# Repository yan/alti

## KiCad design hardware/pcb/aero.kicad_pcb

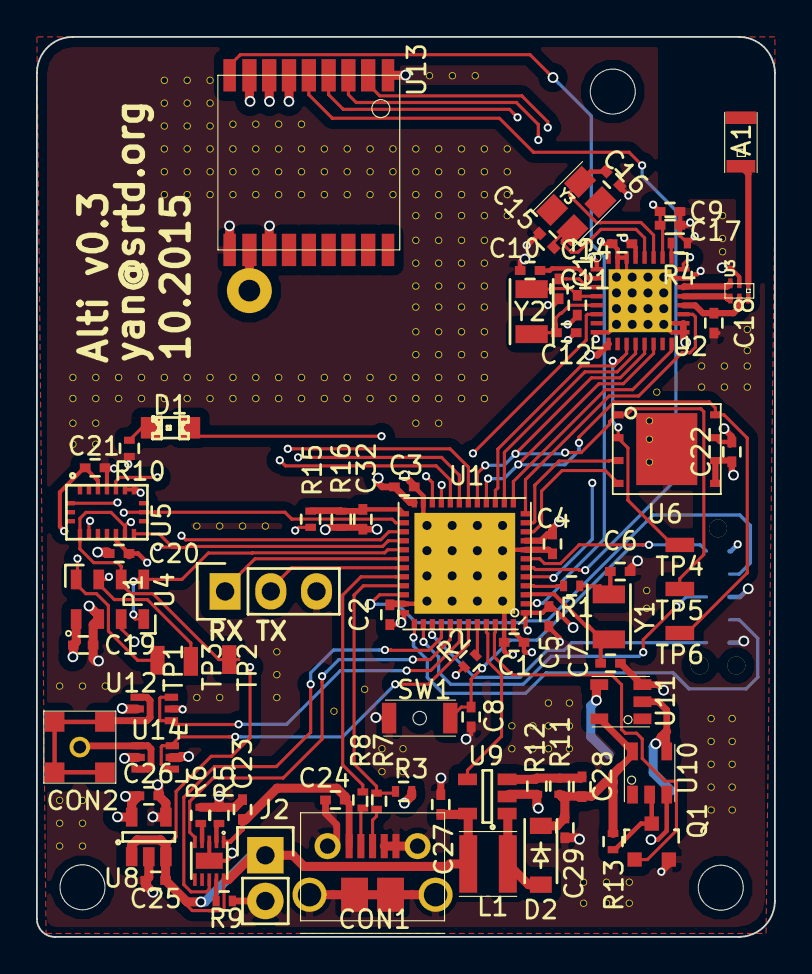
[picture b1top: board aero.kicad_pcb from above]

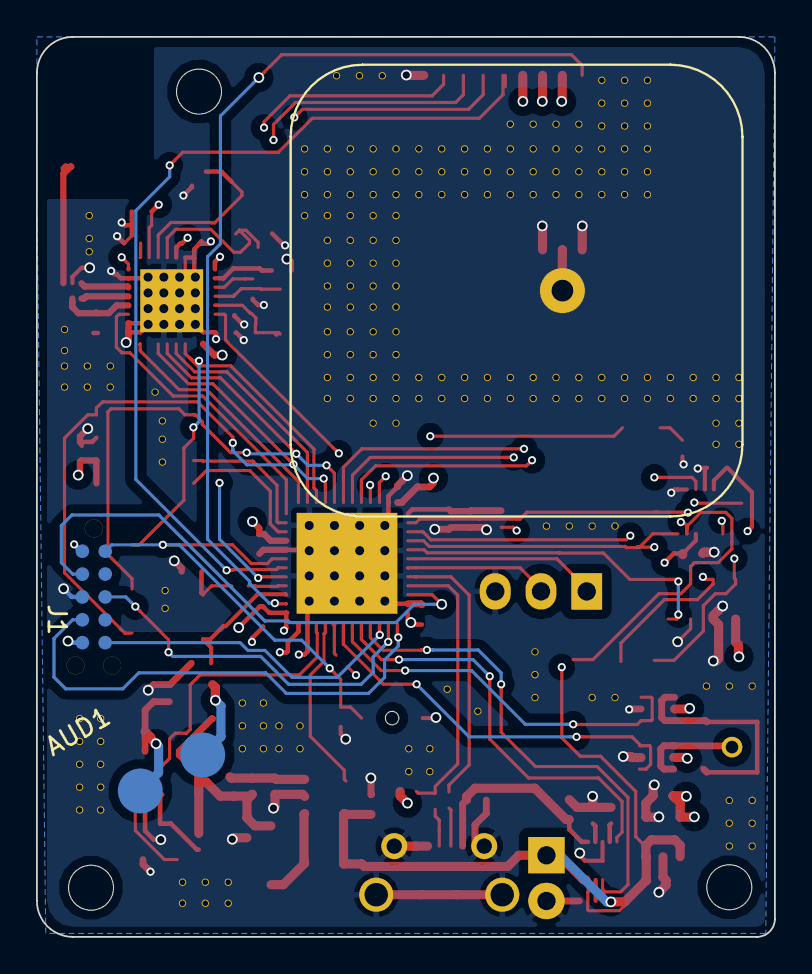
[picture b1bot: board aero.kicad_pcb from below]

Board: 4 copper layers, 41.0 x 50.0 mm, 81 parts (3 on the bottom side), 70 nets.

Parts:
A1: 2450AT18A100
A2: U.FL_Antenna; CGGP.25.4.A.02
AUD1: PIEZO; Piezo_Solder_Conn
C1, C2, C3, C4, C9, C10, C14, C19, C20, C21, C22, C29, C32: 100nF; C_0402
C5, C23, C24, C25: 1uF; C_0402
C6, C7: 9pF; C_0402
C8: 10nF; C_0402
C11, C12: 15pF; C_0402
C13: 33nF; C_0402
C15, C16: 12pF; C_0402
C17: 1.0nF; C_0402
C18: 2.2nF; C_0402
C26: 2.2uF; C_0402
C27: 4.7uF; C_0402
C28: 22pF; C_0402
CON1: USB-MICRO-B; WM1399CT-ND
CON2: MMCX_CONN; CONMMCX002-SMD
D1: LED; LED-0805
D2: D_Schottky; SOD-123
J1: CORTEX_DBG_CONN; TC2050-IDC-NL
J2: LiPoly_Conn; Pin_Header_Straight_1x02
L1: 10u; IND-744029100
P1: CONN_01X03; Pin_Header_Straight_1x03
Q1: BSS138; SOT-23
R1: 0; R_0402
R2, R9: 10k; R_0402
R3: 1.5k; R_0402
R4: 22k; R_0402
R5: 825; R_0402
R6: 2k; R_0402
R7, R8: 22; R_0402
R10: 200; R_0402
R11: 2.21m; R_0402
R12: 309k; R_0402
R13: 30k; R_0402
R15, R16: 10m; R_0402
SW1: SW_PUSH; B3U-1000P
TP1, TP2, TP3, TP4, TP5, TP6: Test_Point; TP_0603
U1: STM32L151C8; UFQFPN48
U2: nRF8001; QFN-32-1EP_5x5mm_Pitch0.5mm
U3: 2450BM14A0002
U4: ms5611
U5: BMX055
U6: AT45DB321E; UDFN-8
U7: BQ24040DSQ; WSON-10-1EP
U8: TPS783; SOT-23-5
U9: TPS61041; SOT-23-5
U10, U11: BU4SU69G2; SSOP-5
U12, U14: NC7WZ17; SC-70-6
U13: u-blox_max-7c/q; ublox_MAX7
Y1: Crystal; Crystal_32768_FC-135R
Y2: 32.768KHz; Crystal_32768_FC-135R
Y3: 16MHz; Crystal_TSX_3225

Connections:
+3V: C1.1, C2.1, C3.1, C4.1, C5.1, C9.1, C14.1, C17.1, C19.1, C20.1, C21.1, C22.1, C26.1, J1.1, R3.1, U1.1, U1.9, U1.24, U1.36, U1.48, U2.1, U2.9, U2.24, U2.26, U2.29, U4.1, U5.3, U5.13, U6.5, U6.6, U8.5, U12.5, U13.6, U13.7, U13.8, U14.5
+10V: C28.1, C29.1, D2.1, R11.1, R13.1, U10.5, U11.5
/GPS/EXT_INT: U1.6, U13.5
/GPS/RESET: U1.2, U13.9
/GPS/TIMEPULSE: U1.5, U13.4
/at45db321e/MISO: TP6.1, U1.16, U2.14, U6.8
/at45db321e/MOSI: TP5.1, U1.17, U2.13, U6.1
/at45db321e/SCK: TP4.1, U1.15, U2.11, U6.2
/at45db321e/~CS: U1.10, U6.4
/at45db321e/~RESET: U1.11, U6.3
/bmx055/ACC_SEL: U1.18, U5.16
/bmx055/GYRO_SEL: U1.19, U5.5
/bmx055/MAG_SEL: U1.20, U5.20
/bmx055/MISO: TP2.1, U1.27, U4.6, U5.12, U5.17
/bmx055/MOSI: TP3.1, U1.28, U4.7, U5.11
/bmx055/SCK: TP1.1, U1.26, U4.8, U5.9
/nRF8001/~RDYN: U1.13, U2.16
/nRF8001/~REQN: U1.14, U2.12
/nRF8001/~RESET: U1.12, U2.19
/power/USB_D+: R3.2, R8.1, U1.33
/power/USB_D-: R7.1, U1.32
/warn/PIEZO_EN: U1.45, U9.4
/warn/PIEZO_OUT: Q1.1, U1.46
/warn/STATUS_LED: D1.2, U1.22
/warn/WARN_LED_A: U1.42, U12.1, U12.3
/warn/WARN_LED_B: U1.43, U14.1, U14.3
BATT_SENSE: C32.2, R15.1, R16.2, U1.25
GND: C1.2, C2.2, C3.2, C4.2, C5.2, C6.2, C7.1, C8.2, C9.2, C10.2, C11.2, C12.2, C13.2, C14.2, C15.1, C16.1, C17.2, C18.2, C19.2, C20.2, C21.2, C22.2, C23.2, C24.2, C25.2, C26.2, C27.2, C29.2, C32.1, CON1.4, CON1.5, CON1.6, CON1.7, CON1.8, CON1.9, CON1.10, CON1.11, J1.3, J1.5, J2.2, P1.3, Q1.2, R2.2, R4.1, R5.2, R6.2, R9.1, R10.1, R12.2, R16.1, SW1.2, U1.8, U1.23, U1.35, U1.47, U1.49, U2.8, U2.17, U2.18, U2.23, U2.30, U2.31, U2.33, U3.2, U4.2, U4.3, U5.4, U5.6, U5.7, U6.7, U7.3, U7.11, U8.2, U8.4, U9.2, U10.3, U11.3, U12.2, U13.1, U13.10, U13.12, U14.2
GPS_RX: P1.1, U1.30, U13.3
GPS_TX: P1.2, U1.31, U13.2
MS5611_EN: U1.29, U4.4, U4.5
NRF8001_ACTIVE: U1.21, U2.6
unnamed: A1.1, U3.1
unnamed: A2.1, U13.11
unnamed: AUD1.1, U11.4
unnamed: AUD1.2, U10.4, U11.2
unnamed: C6.1, R1.1, Y1.1
unnamed: C7.2, U1.3, Y1.2
unnamed: C10.1, U2.2
unnamed: C11.1, U2.4, Y2.1
unnamed: C12.1, U2.5, Y2.2
unnamed: C13.1, U2.3
unnamed: C15.2, U2.28, Y3.1
unnamed: C16.2, U2.27, Y3.2
unnamed: C18.1, U2.20, U3.5
unnamed: C23.1, C24.1, CON1.1, U7.1
unnamed: C28.2, R11.2, R12.1, U9.3
unnamed: CON1.2, R7.2
unnamed: CON1.3, R8.2
unnamed: CON2.1, U14.4, U14.6
unnamed: CON2.2, CON2.3, CON2.4, CON2.5, U12.4, U12.6
unnamed: D1.1, R10.2
unnamed: D2.2, L1.1, U9.1
unnamed: J1.2, U1.34
unnamed: J1.4, U1.37
unnamed: J1.8, U1.38
unnamed: Q1.3, R13.2, U10.2
unnamed: R1.2, U1.4
unnamed: R2.1, U1.44
unnamed: R4.2, U2.25
unnamed: R5.1, U7.2
unnamed: R6.1, U7.4
unnamed: R9.2, U7.9
unnamed: U2.21, U3.4
unnamed: U2.22, U3.3
SWO: J1.6, U1.39
Vbatt: C25.1, C27.1, J2.1, L1.2, R15.2, U7.10, U8.1, U8.3, U9.5
~CHG: U1.40, U7.8
~NRST: C8.1, J1.10, SW1.1, U1.7
~PG: U1.41, U7.5

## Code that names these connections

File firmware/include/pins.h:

#ifndef __PINS_DEF
#define __PINS_DEF
/****************************************************************/
/** AUTOGENERATED from ../include/pins.def. DO NOT EDIT *********/
/****************************************************************/

#if defined(STM32L1) && defined(OPENCM3)
#  include <stm32l1_opencm3_pins.h>
#elif defined(STM32L1) && defined(STM32_STDPERIPH_LIB)
#  include <stm32l1_stdperiphlib_pins.h>
#elif TESTING == 1
#  include <empty_pins.h>
#else
#  error "Unsupprted architecture"
#endif

#define PIEZO_OUT_TIMER                 TIM4
#define PIEZO_OUT_CHANNEL               TIM_OC(4)
#define PIEZO_OUT_AF                    GPIO_AF2
#define STATUS_LED_TIMER                TIM2
#define STATUS_LED_CHANNEL              TIM_OC(4)
#define STATUS_LED_AF                   GPIO_AF1
#define BT_STORE                        SPI1
#define BT_STORE_GPIO                   GPIO(A)
#define BT_STORE_PINS                   (PIN(7)|PIN(6)|PIN(5))
#define SENSORS                         SPI2
#define SENSORS_GPIO                    GPIO(B)
#define SENSORS_PINS                    (PIN(15)|PIN(14)|PIN(13))
#define UBLOX_UART                      USART1
#define UBLOX_UART_GPIO                 GPIO(A)
#define UBLOX_UART_PINS                 (PIN(10)|PIN(9))
#define NRF8001_LSB                     1
#define NRF8001_BUS                     BT_STORE
#define ADESTO_FLASH_LSB                1
#define ADESTO_FLASH_BUS                BT_STORE
#define MS5611_LSB                      1
#define MS5611_BUS                      SENSORS
#define BMX055_LSB                      1
#define BMX055_BUS                      SENSORS
#define UBLOX_MAX7_LSB                  1
#define UBLOX_MAX7_BUS                  UBLOX_UART
#define ADESTO_FLASH_CS                 PIN(0)
#define ADESTO_FLASH_CS_GPIO            GPIO(A)
#define ADESTO_FLASH_RESET              PIN(1)
#define ADESTO_FLASH_RESET_GPIO         GPIO(A)
#define NRF8001_RST                     PIN(2)
#define NRF8001_RST_GPIO                GPIO(A)
#define NRF8001_RDYN                    PIN(3)
#define NRF8001_RDYN_GPIO               GPIO(A)
#define NRF8001_REQN                    PIN(4)
#define NRF8001_REQN_GPIO               GPIO(A)
#define BT_STORE_SCK                    PIN(5)
#define BT_STORE_SCK_GPIO               GPIO(A)
#define BT_STORE_MISO                   PIN(6)
#define BT_STORE_MISO_GPIO              GPIO(A)
#define BT_STORE_MOSI                   PIN(7)
#define BT_STORE_MOSI_GPIO              GPIO(A)
#define MS5611_EN                       PIN(8)
#define MS5611_EN_GPIO                  GPIO(A)
#define UBLOX_UART_TX                   PIN(9)
#define UBLOX_UART_TX_GPIO              GPIO(A)
#define UBLOX_UART_RX                   PIN(10)
#define UBLOX_UART_RX_GPIO              GPIO(A)
#define BMX055_EN_ACC                   PIN(0)
#define BMX055_EN_ACC_GPIO              GPIO(B)
#define BMX055_EN_GYRO                  PIN(1)
#define BMX055_EN_GYRO_GPIO             GPIO(B)
#define BMX055_EN_MAG                   PIN(2)
#define BMX055_EN_MAG_GPIO              GPIO(B)
#define CHG                             PIN(4)
#define CHG_GPIO                        GPIO(B)
#define PG                              PIN(5)
#define PG_GPIO                         GPIO(B)
#define WARN_LED_A                      PIN(6)
#define WARN_LED_A_GPIO                 GPIO(B)
#define WARN_LED_B                      PIN(7)
#define WARN_LED_B_GPIO                 GPIO(B)
#define PIEZO_EN                        PIN(8)
#define PIEZO_EN_GPIO                   GPIO(B)
#define PIEZO_OUT                       PIN(9)
#define PIEZO_OUT_GPIO                  GPIO(B)
#define NRF8001_ACTIVE                  PIN(10)
#define NRF8001_ACTIVE_GPIO             GPIO(B)
#define STATUS_LED                      PIN(11)
#define STATUS_LED_GPIO                 GPIO(B)
#define BATT_SENSE                      PIN(12)
#define BATT_SENSE_GPIO                 GPIO(B)
#define SENSORS_SCK                     PIN(13)
#define SENSORS_SCK_GPIO                GPIO(B)
#define SENSORS_MISO                    PIN(14)
#define SENSORS_MISO_GPIO               GPIO(B)
#define SENSORS_MOSI                    PIN(15)
#define SENSORS_MOSI_GPIO               GPIO(B)
#define UBLOX_MAX7_RESET                PIN(13)
#define UBLOX_MAX7_RESET_GPIO           GPIO(C)
#define UBLOX_MAX7_TIMEPULSE            PIN(0)
#define UBLOX_MAX7_TIMEPULSE_GPIO       GPIO(H)
#define UBLOX_MAX7_EXT_INT              PIN(1)
#define UBLOX_MAX7_EXT_INT_GPIO         GPIO(H)
#endif /* __PINS_DEF */

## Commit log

2015-03-21 Added submodules
2015-03-21 Created firmware dir
2015-03-21 Added README
2015-03-21 Build FreeRTOS
2015-03-21 Update to build system
2015-03-22 Now sort of builds libopencm3
2015-03-22 Build system now works-ish
2015-03-22 Cleaner build system + more filler
2015-03-22 Comments and start of event system
2015-03-22 New dirs + makefile updates
2015-03-22 Starting bringing over i2c/ble/etc functionality
2015-03-22 Fix makefile rules for flashing and rename
2015-03-22 More sane build system
2015-03-22 Starting event handling and state definition
2015-03-22 Added blink task; config works
2015-03-22 Blink LED when nrf8001 is ready
2015-03-22 NRF8001 work
2015-03-23 BLE work
2015-03-23 Updating build system
2015-03-23 Moved ble gpio to header
2015-03-23 Added kicad project + BMI055 footprint
2015-03-24 Fix EXTI priority and enable SYSCFG clock (RDYN works)
2015-03-24 Correctly exchanging messages, but main_queue isn't receiving correctly
2015-03-24 Send NRF8001 events to main queue
2015-03-25 Add fault handlers and update the build system
2015-03-25 Moved BLE initialization to BLE task, but still failing on setup
2015-03-25 CSB updates
2015-03-25 Debug output updates
2015-03-26 We can now reliably send commands to nrf8001
2015-03-26 /now/ setup works
2015-03-26 More BLE state machine work
2015-03-27 Moved session initiation to nrf8001.c
2015-03-27 Move to Nordic's official header files
2015-03-27 Fix cmd sending bug
2015-03-28 Various changes
    * Decrease main task size
    * Clean up BLE code
2015-03-28 i2c address reorg
2015-03-28 Adding new services.h
2015-03-28 Aero now being detected
2015-03-28 Can now push data to an iphone
2015-03-29 Moved globals to a single struct; start of baro task
2015-03-30 We can now stream pressure via BLE
2015-03-30 Rename status task+types to alert
2015-03-30 Added BMX055 footprint
2015-03-31 Added SON-10 footprint for TI lipoly charger ic
2015-03-31 Make the alert task handle other types of alerts
2015-03-31 Add a package outline for (W)SON-10 footprint
2015-03-31 Moved ble state out of static
2015-03-31 Added stm32l151 (UFQFPN48) footprint
2015-03-31 Added STM32L151C8 component to lib
2015-03-31 Added BMX055 to components lib
2015-03-31 Refactor i2c init
2015-03-31 Added UDFN-8 footprint for AT45DB321E
2015-03-31 Added AT45DB321E component
2015-03-31 New empty files for flash ic
2015-04-01 Adding hardware docs
2015-04-01 Added nRF8001 shematic symbol
2015-04-01 Added more stm32l1 docs
2015-04-01 Added nrf8001 sheet
2015-04-01 Added xtal footprints
2015-04-03 version 1 of layout
2015-04-06 pcb updates
2015-04-07 Added a list of parts->pins mapping
2015-04-10 Added stm32l1 pins spreadsheet
2015-04-10 PCB updates, new docs, file reorg
2015-04-10 Removed nRF8001 connections; beginning eventual design
2015-04-14 Updated pin assignments in spreadsheet
2015-04-15 Added mcu, connected nrf8001 and flash, new footprint, other changes
2015-04-15 more progress on hw
2015-04-16 More work on power section
2015-04-16 added sensor connections
2015-04-16 spreadsheet+schem updates
2015-04-22 Lots of hw changes (warn circuits, footprint, etc)
2015-04-23 schematic updates
2015-04-24 Added some testpoints
2015-04-27 schematic nearing completion
2015-04-28 Deleted nrf8001 breakout
2015-04-28 Added component values
2015-04-28 more changes
2015-05-07 mega commit
2015-05-08 Finished layout
2015-06-20 ms5611 and nrf8001 in SPI mode both work on the new dev board
2015-06-21 Added hardware errata file
2015-06-21 Fix endianness of SPI link
2015-06-21 fixed a few known pcb issues
2015-06-22 Cleaned up SPI usage
2015-06-22 Began bmx055 support
2015-06-22 hw fixes
2015-06-23 Not using bmx055 yet, add protected flash buffer, other changes
2015-06-23 start adding flash constants
2015-06-25 Added first ios client skeleton
2015-06-25 Cleanup
2015-07-01 recent changes
2015-07-10 Large commit (bad form :() starting HAL and various cleanups
2015-07-10 rename baro task to sensor task
2015-07-14 Plenty of updates, but writing and reading from flash now works
2015-07-15 arch reorg
2015-07-17 spi/arch updates
2015-07-17 add copyright comments
2015-07-18 more hal updates
2015-07-20 more ios mucking about
2015-07-20 committing hardware updates (probably unnecessary)
2015-07-21 more reorg
2015-07-21 more reorg; cleanups
2015-07-21 imported stm32l1 std periph lib & reorg
2015-07-21 ios client updates
2015-07-22 all arch-specific functions are now in hal.h
2015-07-22 Logging sort of works!
2015-07-22 Started persistent config support
2015-07-28 pre major restructuring commit
2015-07-30 committing before shit starts breaking (pcbnew)
2015-07-30 remove ble.h
2015-07-30 no more ble.[ch]
2015-07-30 more progress on new layout
2015-07-31 more pcb rework
2015-08-06 ver2 is nearing completion.
2015-08-06 more firmware work
2015-08-07 no more vias under pads
2015-08-19 pre-antenna reorg commit
2015-08-19 rewired sensors + gps
2015-09-09 began cleanup of build system
2015-09-12 Build system /much/ better now
2015-09-13 build system improvements
2015-09-14 lots of changes (headers, build sys, others)
2015-09-15 Add a reset cmd to gdb_commands
2015-09-15 First version of the antlr grammar
2015-09-15 More pingen work
2015-09-15 Makefile updates + pins.h generator sort of works
2015-09-16 Updated pin references
2015-09-16 Updated pin gen script
2015-09-17 moved balun further from nrf8001
2015-09-30 Intermediate commit
2015-10-16 Can now build a native aero lib
2015-10-23 pre-net import
2015-10-24 passes DRC with stitching
2015-10-24 now with normal vias
2015-10-24 hw check in (v3 sent to oshpark)
2015-10-28 updated gitignore
2015-10-28 remove backup files from git
2015-10-29 remove i2c from repo
2015-11-06 reformatting + few changes
2015-11-09 ublox updates
2015-11-09 add docs
2015-11-09 update spi api
2015-11-09 sort ublox constants
2015-11-09 add desktop ublox testing code
2015-11-09 fix build
2015-11-15 intermediate commit, every sensor works (!!)
2015-11-16 various updates + new gps task
2015-11-17 more sensor work
2015-11-17 makefile update && start of sensor packet def
2015-11-17 update gitignore
2015-11-18 committing yesterdays code; uart handler+co
2015-11-19 First draft (Untested) of usart isr
2015-11-19 intermediate commit - uart works with isrs and switching baud rates works
2015-11-24 intermediate
2015-11-25 ublox updates; stdperiph lib supported but untested
2015-12-02 committing intermediate stdperiph port work
2015-12-02 start on sample header
2015-12-08 committing old changes
2015-12-16 remove tags
2015-12-16 Can now build for x64
2015-12-16 fix some asserts
2015-12-16 steps towards being able to test
2015-12-23 intermediate commit [doesnt build]
2015-12-26 more intermediate
2015-12-30 Start of CMake support
2015-12-30 minor changes
2016-01-05 cmake updates
2016-01-10 mega commit; saving progress
2016-01-11 ble+gps works with stm32periph!
2016-01-12 move to cmake
2016-01-12 CMake updates; testing builds; some C linkage
2016-01-12 centralized freertos includes
2016-01-12 ignore dirty submodules
2016-01-13 [wip] pushing while working out linking issues
2016-01-14 fixed build
2016-01-14 First few actual tests
2016-01-14 add local gtest
2016-01-14 cmake
2016-01-15 [wip] rewriting logging layer; continuing tests
2016-01-15 Logger functionality + more tests
2016-01-15 Change definition of the sentinel
2016-01-16 Few logger docs
2016-01-25 some reorg + bufio fixes + tests
2016-01-26 new functionality ; more tests
2016-01-26 no more empty event
2016-01-26 Added code for a ble debug tool
2016-02-01 dirty, but ble debug qt client gets characteristics
2016-02-01 cleanups
2016-02-06 update ble config
2016-02-10 can now stream simple packets!
2016-02-11 Add client support for larger packets [hack; will rewrite]
2016-02-11 Send larger packets
2016-02-14 Restructure some BLE code
2016-05-28 should have committed earlier
2016-06-18 services.h update to support new channel
2016-06-27 Start of config rearch
2016-06-27 redo config packets
2016-06-27 Warnings++
2016-07-07 Fixed logger behavior
2016-07-14 overdue commit
2016-07-15 support cleanup
2016-08-03 Import qt quick client
2016-08-03 Update cmakelists
2016-08-03 Various changes (see commit msg)
    * Fix mutex protection for SPI bus
    * Fix BLE (!!)
    * Add a counter
    * Add a pin_get() function
    * Rework config message handling
    * Update nRF8001 handling
2016-08-03 Build/test updates
2016-08-03 Test some settings code
2016-08-03 Testing removing the anon struct
2016-08-04 Removing external freertos submodule
2016-08-04 New freertos submodule
2016-08-12 Implement nRF8001 credit counting
2016-08-12 Store BLE struct inline with globals
2016-08-12 Update spi bus locking
2016-08-12 Misc clean ups
2016-08-12 BLE structure and test changes
2016-08-12 BLE tests
2016-08-12 Finalize removal of tx_packet
2016-08-12 Remove extra baro collection
2016-08-12 Start/stop gps again [still broken; ref commit]
2016-08-12 Gitignore update
2016-08-19 Naming update
2016-08-26 Testing, SPI locking, BLE updates
2016-08-26 Client updates
2016-08-26 Fix the linker script
2016-08-26 Add -Os
